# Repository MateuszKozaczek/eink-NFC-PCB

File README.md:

This is PCB project of smart tag for master's degree diploma project

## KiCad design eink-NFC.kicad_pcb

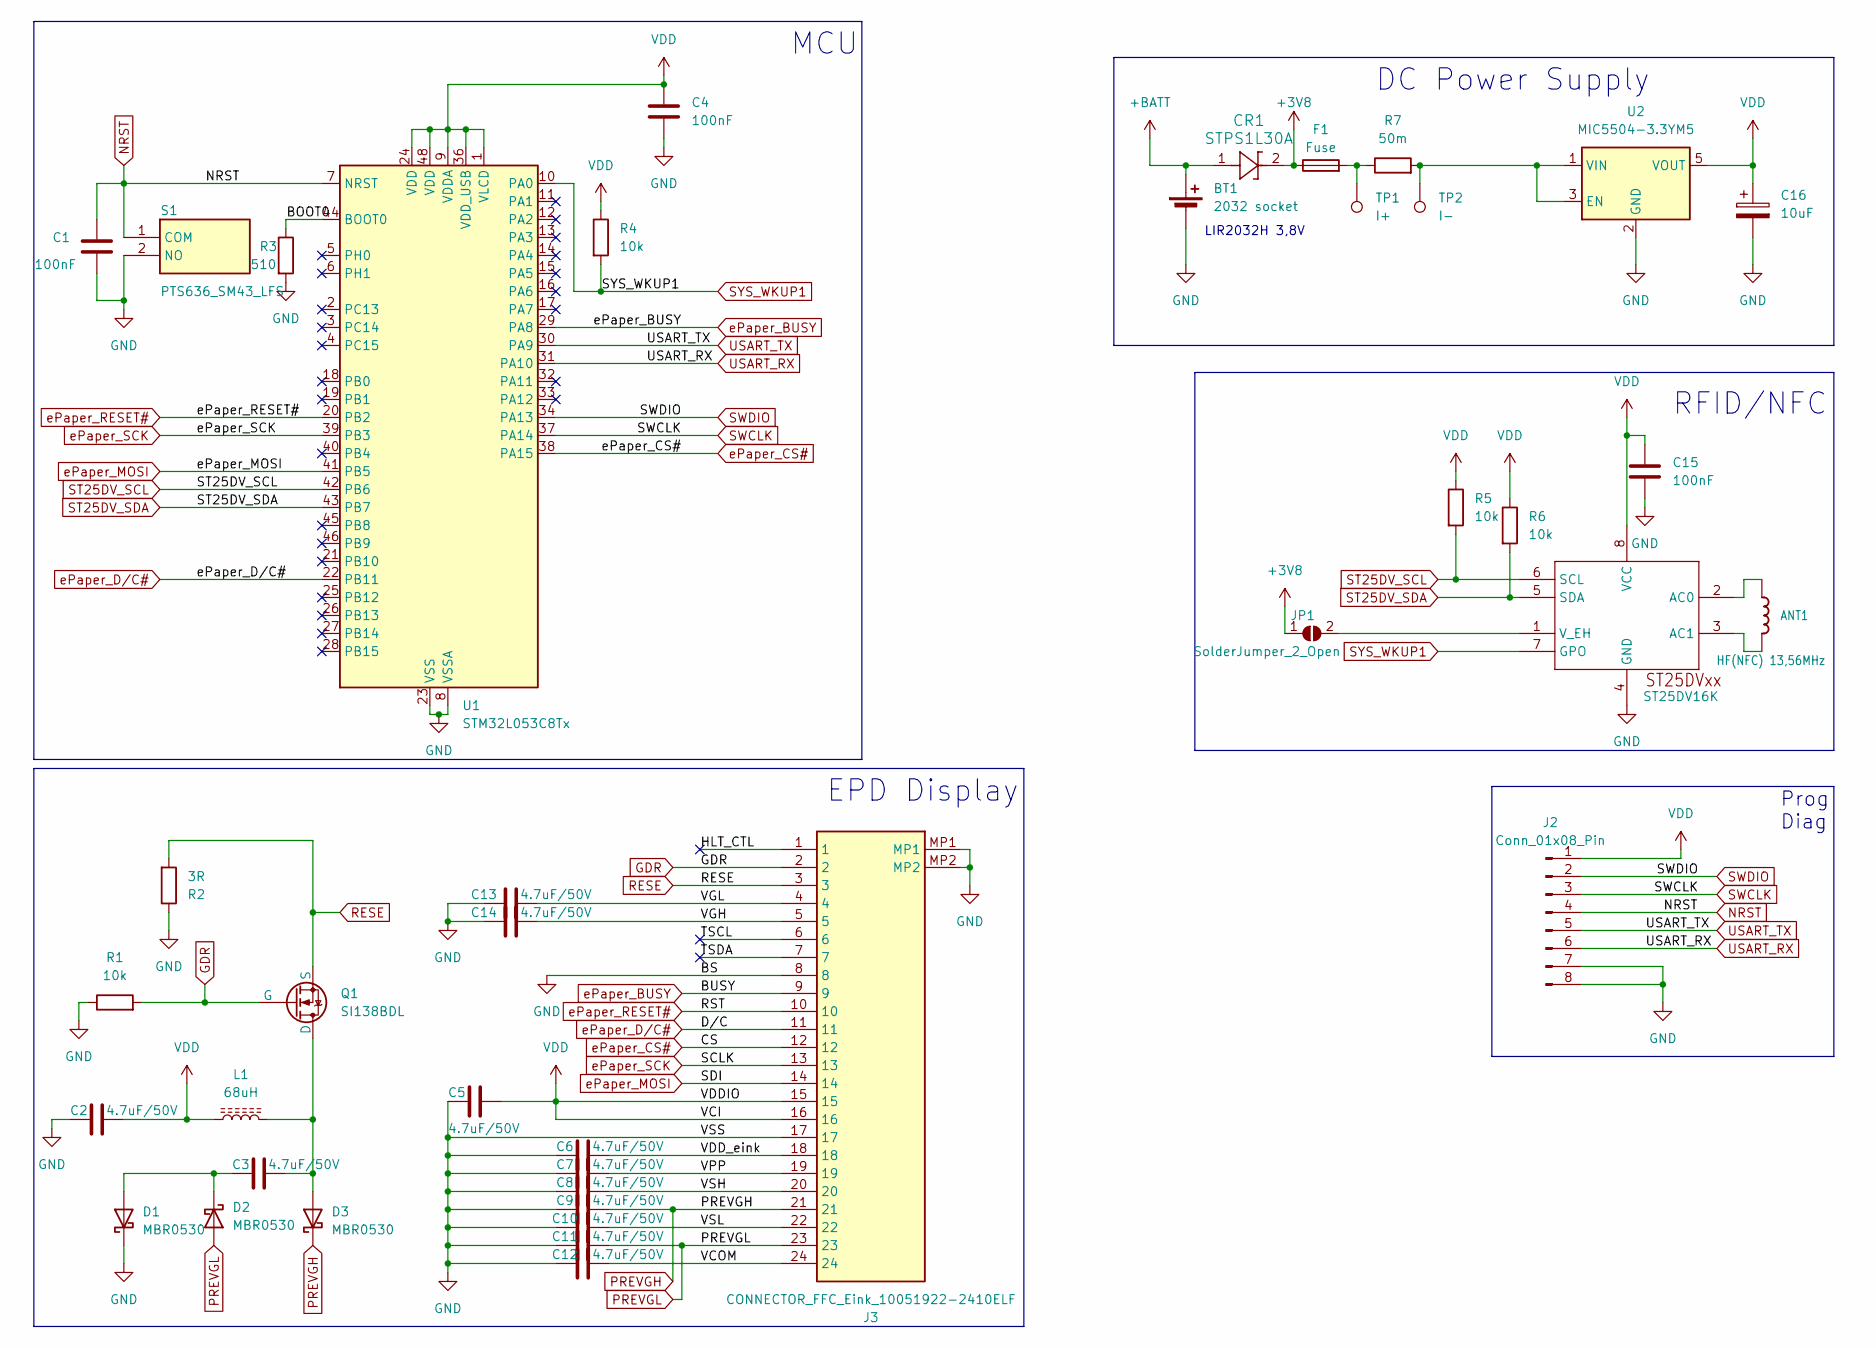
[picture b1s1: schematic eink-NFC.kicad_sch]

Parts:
ANT1: HF(NFC) 13,56MHz; NFCANT_25X15
BT1: 2032 socket; SMTU2032LF
C1, C4, C15: 100nF; C_0805_2012Metric_Pad1.18x1.45mm_HandSolder
C2, C3, C5, C6, C7, C8, C9, C10, C11, C12, C13, C14: 4.7uF/50V; C_0805_2012Metric_Pad1.18x1.45mm_HandSolder
C16: 10uF; CP_Elec_4x5.4
CR1: STPS1L30A; SMA_STM
D1, D2, D3: MBR0530; D_SOD-123
F1: Fuse; Fuse_1206_3216Metric_Pad1.42x1.75mm_HandSolder
J2: Conn_01x08_Pin; PinSocket_1x08_P2.54mm_Vertical
J3: CONNECTOR_FFC_Eink_10051922-2410ELF; 100519222410ELF; Mouser Part Number 649-10051922-2410ELF
JP1: SolderJumper_2_Open; SolderJumper-2_P1.3mm_Open_Pad1.0x1.5mm
L1: 68uH; L_Bourns-SRN4018
Q1: SI138BDL; SOT-323_SC-70_Handsoldering
R1, R4, R5, R6: 10k; R_0805_2012Metric_Pad1.20x1.40mm_HandSolder
R2: 3R; R_0805_2012Metric_Pad1.20x1.40mm_HandSolder
R3: 510; R_0805_2012Metric_Pad1.20x1.40mm_HandSolder
R7: 50m; R_1206_3216Metric_Pad1.30x1.75mm_HandSolder
RF1: ST25DV16K; SOIC-8_3.9x4.9mm_P1.27mm
S1: PTS636_SM43_LFS; PTS636SM43LFS; Mouser Part Number 611-PTS636SM43LFS
TP1: I+; TestPoint_Pad_D3.0mm
TP2: I-; TestPoint_Pad_D3.0mm
U1: STM32L053C8Tx; LQFP-48_7x7mm_P0.5mm
U2: MIC5504-3.3YM5; SOT-23-5

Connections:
+3V8: CR1.2, F1.1, JP1.1 (A)
+BATT: BT1.1 (+), CR1.1
/BOOT0: R3.1, U1.44 (BOOT0)
/HLT_CTL: J3.1
/TSCL: J3.6
/TSDA: J3.7
/VCOM: C12.2, J3.24
/VDD_eink: C6.2, J3.18
/VGH: C14.2, J3.5
/VGL: C13.2, J3.4
/VPP: C7.2, J3.19
/VSH: C8.2, J3.20
/VSL: C10.2, J3.22
GDR: J3.2, Q1.1 (G), R1.2
GND: BT1.2 (-), C1.2, C2.1, C4.2, C5.1, C6.1, C7.1, C8.1, C9.1, C10.1, C11.1, C12.1, C13.1, C14.1, C15.2, C16.2, D1.1 (K), J2.7, J2.8, J3.8, J3.17, J3.MP1, J3.MP2, R1.1, R2.1, R3.2, RF1.4 (GND), S1.2 (NO), U1.8 (VSSA), U1.23 (VSS), U1.35 (VSS), U1.47 (VSS), U2.2 (GND)
NRST: C1.1, J2.4, S1.1 (COM), U1.7 (NRST)
unnamed: ANT1.P$1 (1), RF1.3 (AC1)
unnamed: ANT1.P$2 (2), RF1.2 (AC0)
unnamed: C3.1, D1.2 (A), D2.1 (K)
unnamed: C3.2, D3.2 (A), L1.2, Q1.3 (D)
unnamed: F1.2, R7.1, TP1.1
unnamed: JP1.2 (B), RF1.1 (V_EH)
unnamed: R7.2, TP2.1, U2.1 (VIN), U2.3 (EN)
PREVGH: C9.2, D3.1 (K), J3.21
PREVGL: C11.2, D2.2 (A), J3.23
RESE: J3.3, Q1.2 (S), R2.2
ST25DV_SCL: R5.2, RF1.6 (SCL), U1.42 (PB6)
ST25DV_SDA: R6.2, RF1.5 (SDA), U1.43 (PB7)
SWCLK: J2.3, U1.37 (PA14)
SWDIO: J2.2, U1.34 (PA13)
SYS_WKUP1: R4.2, RF1.7 (GPO), U1.10 (PA0)
USART_RX: J2.6, U1.31 (PA10)
USART_TX: J2.5, U1.30 (PA9)
VDD: C2.2, C4.1, C5.2, C15.1, C16.1, J2.1, J3.15, J3.16, L1.1, R4.1, R5.1, R6.1, RF1.8 (VCC), U1.1 (VLCD), U1.9 (VDDA), U1.24 (VDD), U1.36 (VDD_USB), U1.48 (VDD), U2.5 (VOUT)
ePaper_BUSY: J3.9, U1.29 (PA8)
ePaper_CS#: J3.12, U1.38 (PA15)
ePaper_D/C#: J3.11, U1.22 (PB11)
ePaper_MOSI: J3.14, U1.41 (PB5)
ePaper_RESET#: J3.10, U1.20 (PB2)
ePaper_SCK: J3.13, U1.39 (PB3)

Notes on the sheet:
MCU
RFID/NFC
DC Power Supply
EPD Display
LIR2032H 3,8V
Prog Diag

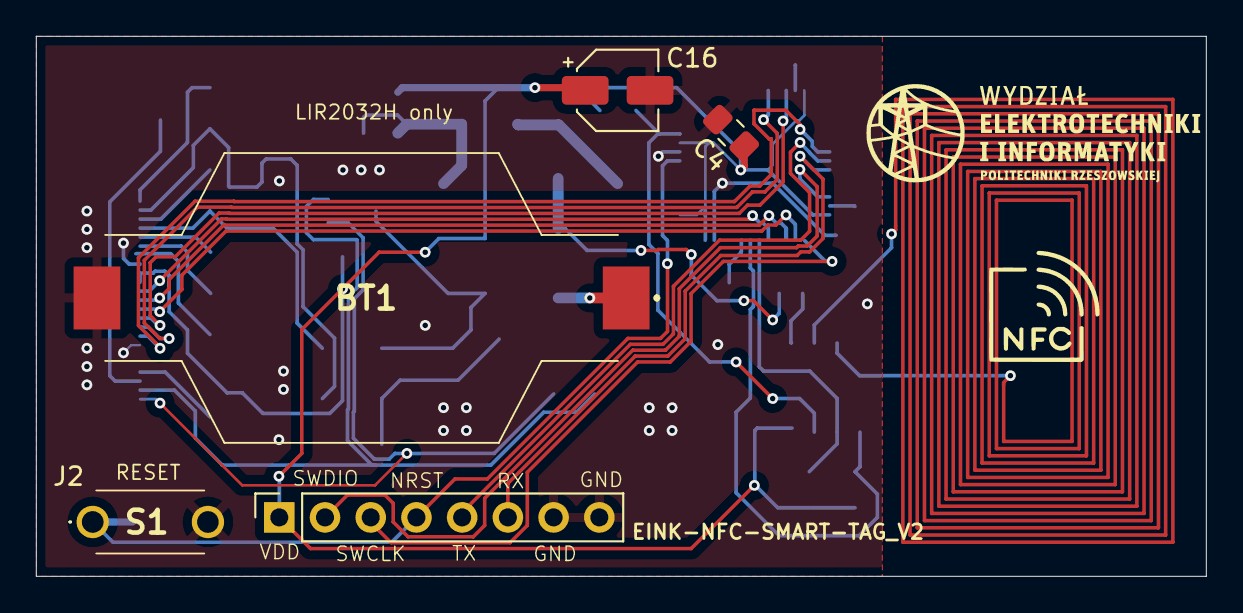
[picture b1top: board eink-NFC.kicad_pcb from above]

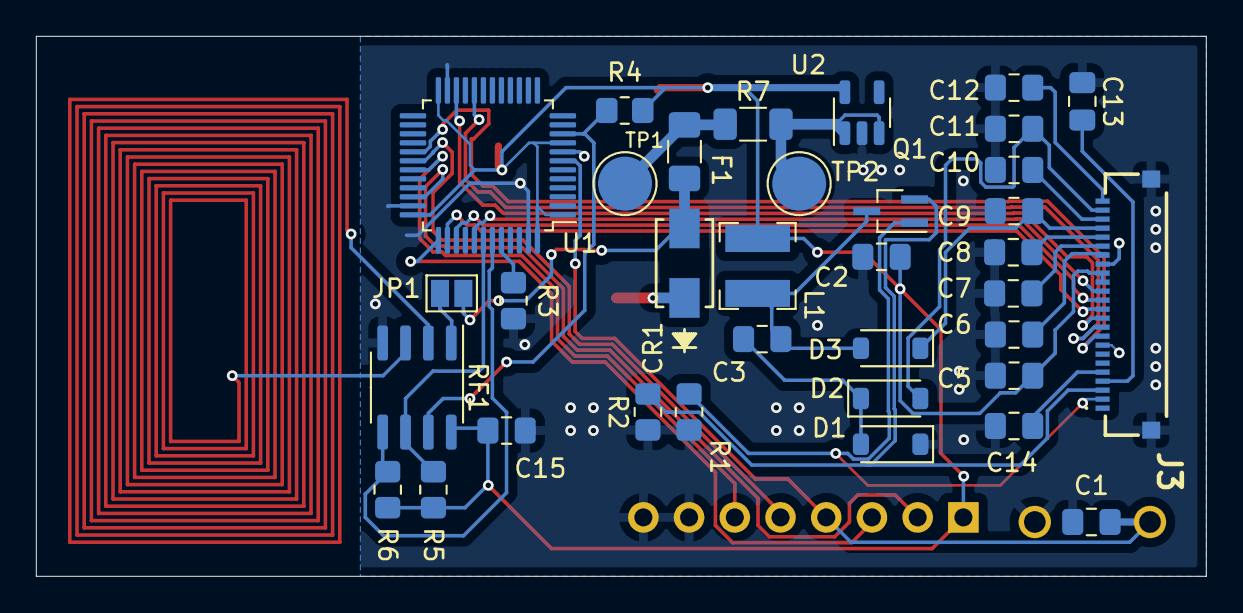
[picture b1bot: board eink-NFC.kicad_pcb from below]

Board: 2 copper layers, 65.0 x 30.0 mm, 41 parts (35 on the bottom side), 37 nets.

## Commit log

2024-09-14 init:commit
